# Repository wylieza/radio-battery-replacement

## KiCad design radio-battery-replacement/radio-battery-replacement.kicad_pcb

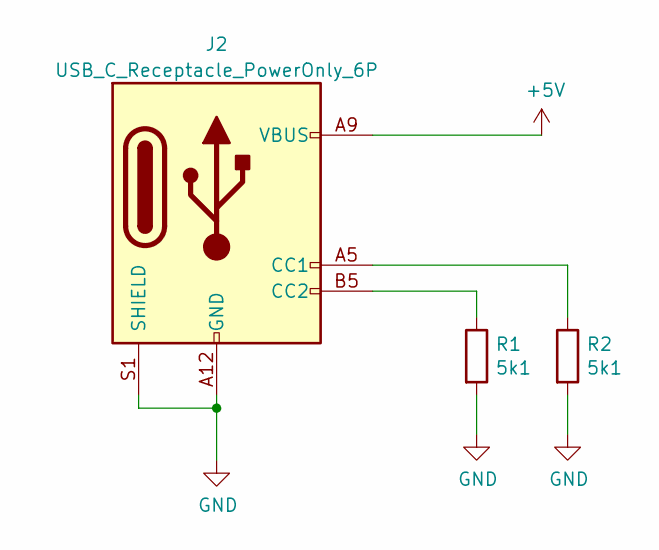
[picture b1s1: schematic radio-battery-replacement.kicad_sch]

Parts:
J2: USB_C_Receptacle_PowerOnly_6P; USB_C_Receptacle_GCT_USB4135-GF-A_6P_TopMnt_Horizontal
R1, R2: 5k1; R_1206_3216Metric_Pad1.30x1.75mm_HandSolder

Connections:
+5V: J2.A9 (VBUS), J2.B9 (VBUS)
GND: J2.A12 (GND), J2.B12 (GND), J2.S1 (SHIELD), R1.2, R2.2
unnamed: J2.A5 (CC1), R2.1
unnamed: J2.B5 (CC2), R1.1

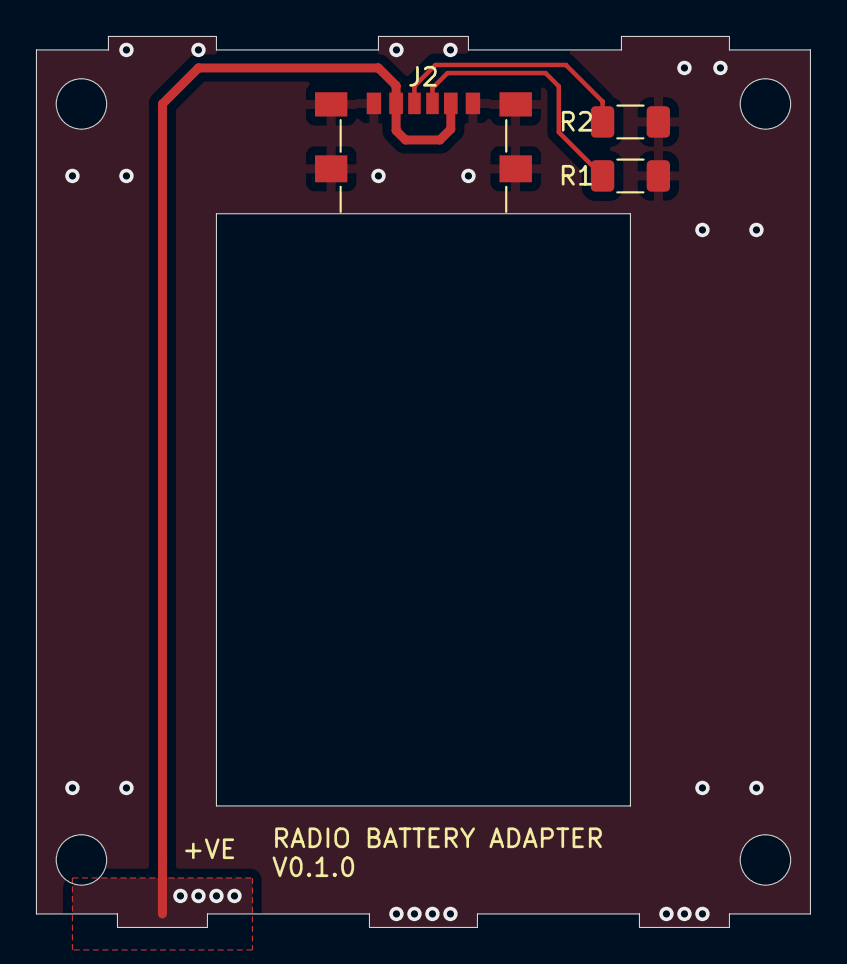
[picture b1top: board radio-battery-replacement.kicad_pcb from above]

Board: 2 copper layers, 43.0 x 49.5 mm, 3 parts (0 on the bottom side), 4 nets.

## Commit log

2024-03-24 initial commit, using kicad version 5.1.5
2024-03-30 version v0.1.0 and fab outputs
